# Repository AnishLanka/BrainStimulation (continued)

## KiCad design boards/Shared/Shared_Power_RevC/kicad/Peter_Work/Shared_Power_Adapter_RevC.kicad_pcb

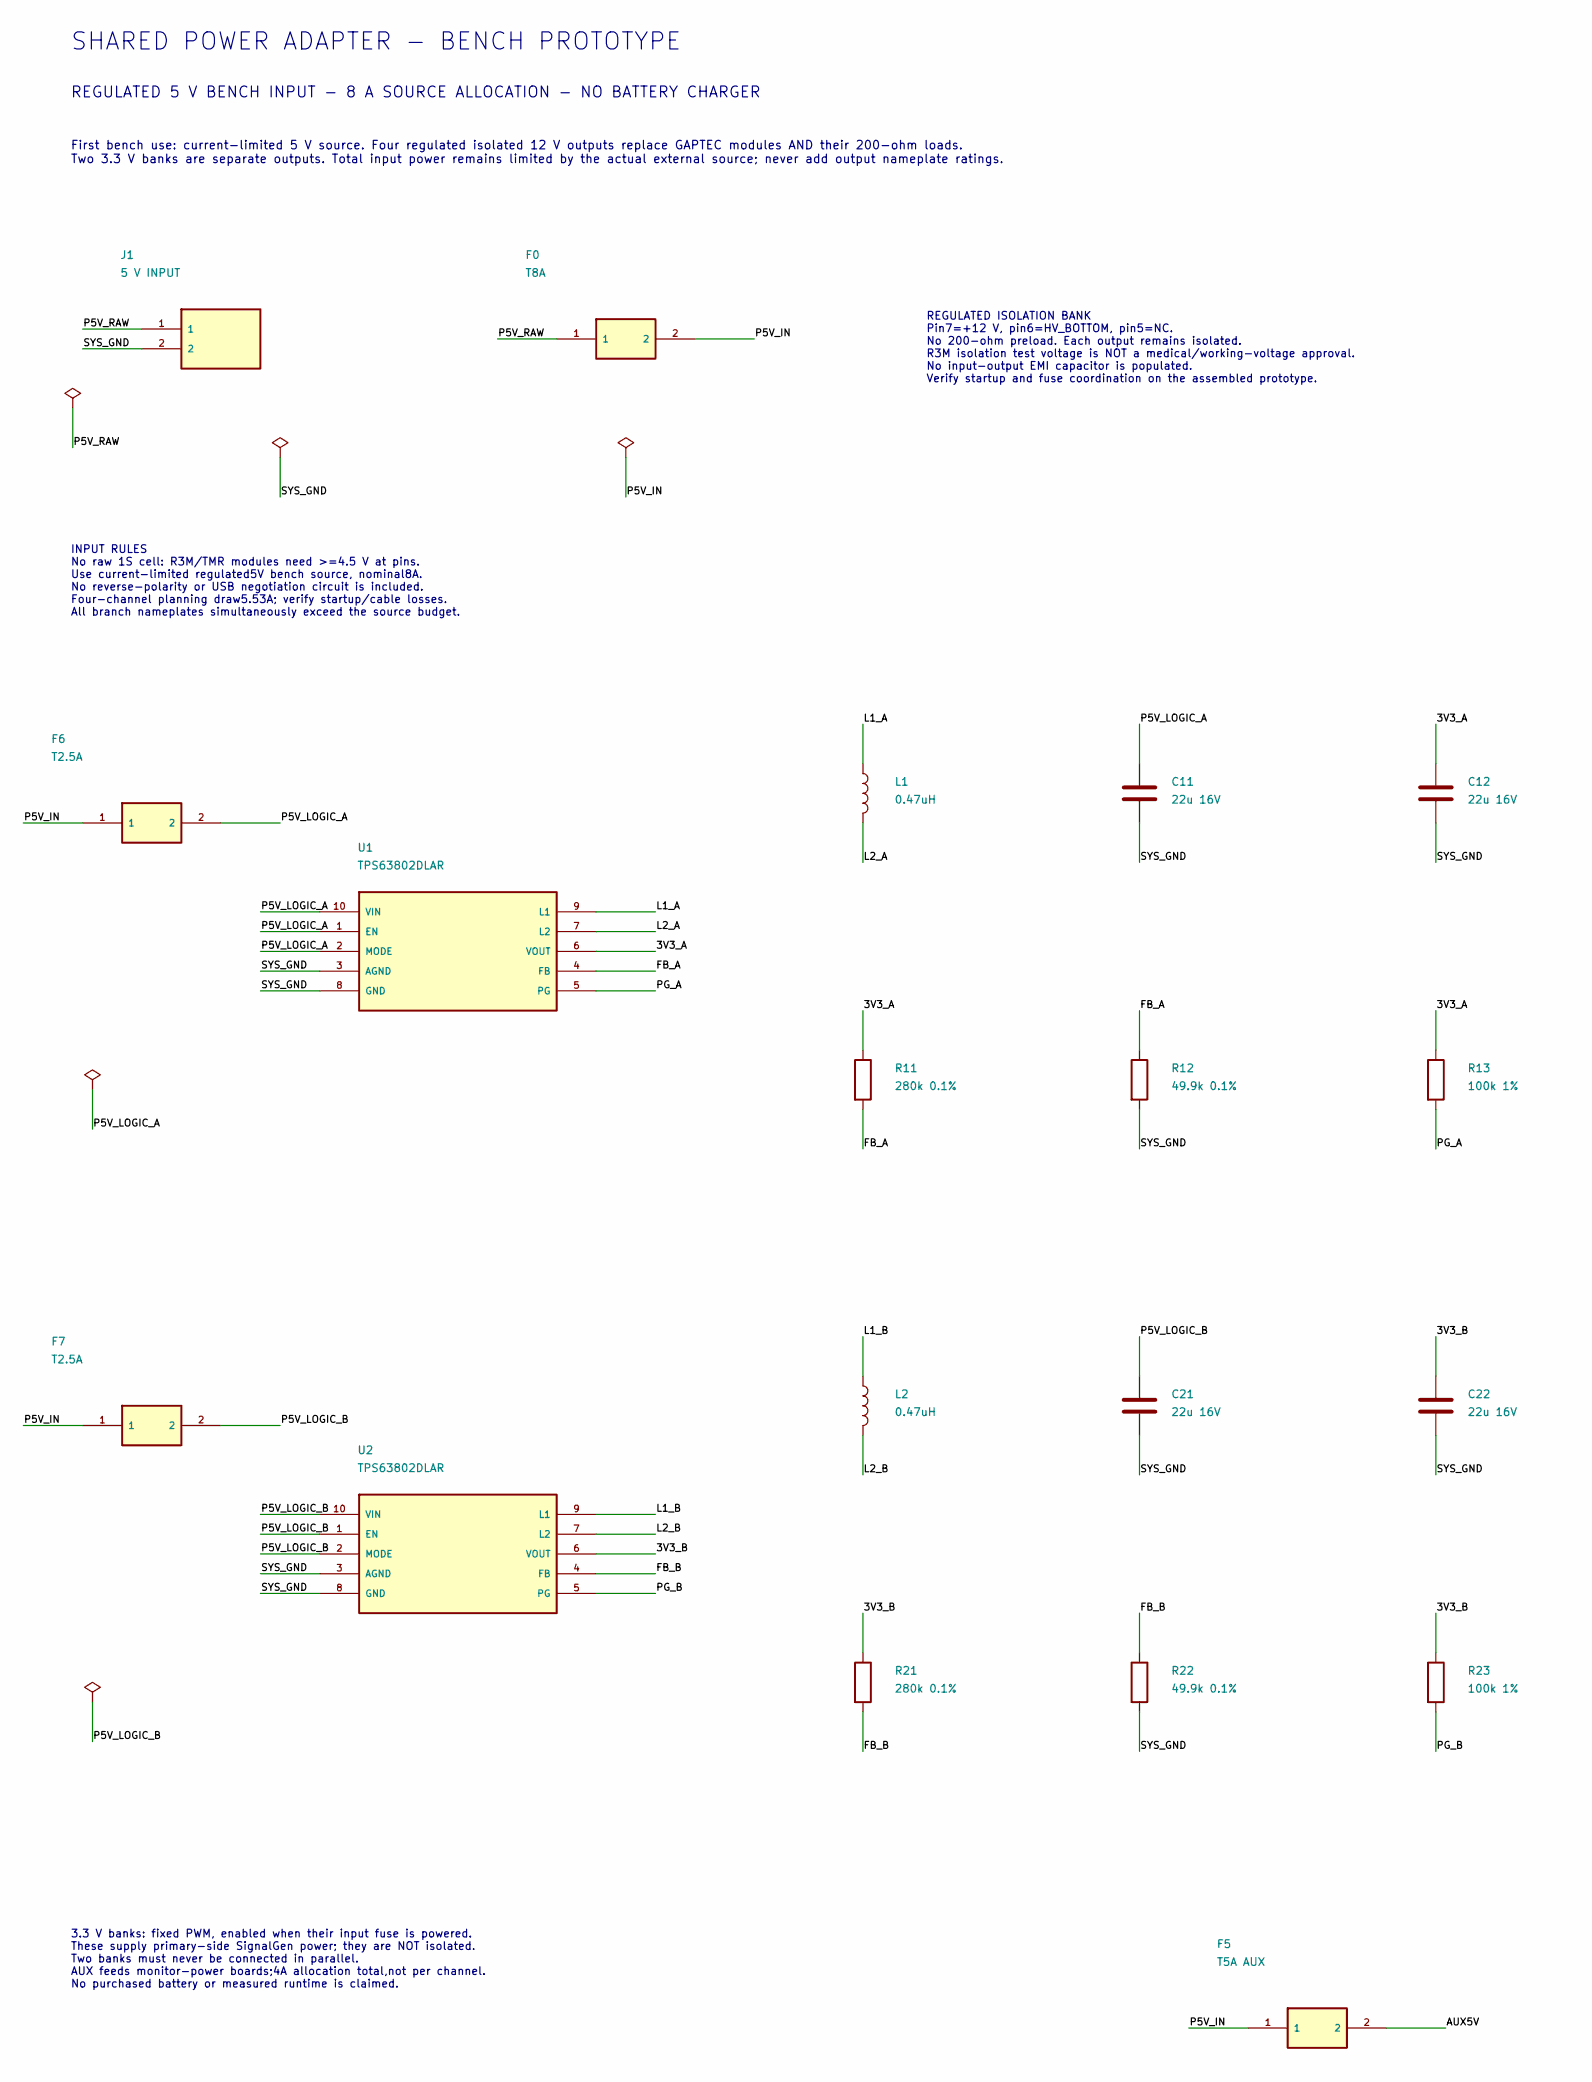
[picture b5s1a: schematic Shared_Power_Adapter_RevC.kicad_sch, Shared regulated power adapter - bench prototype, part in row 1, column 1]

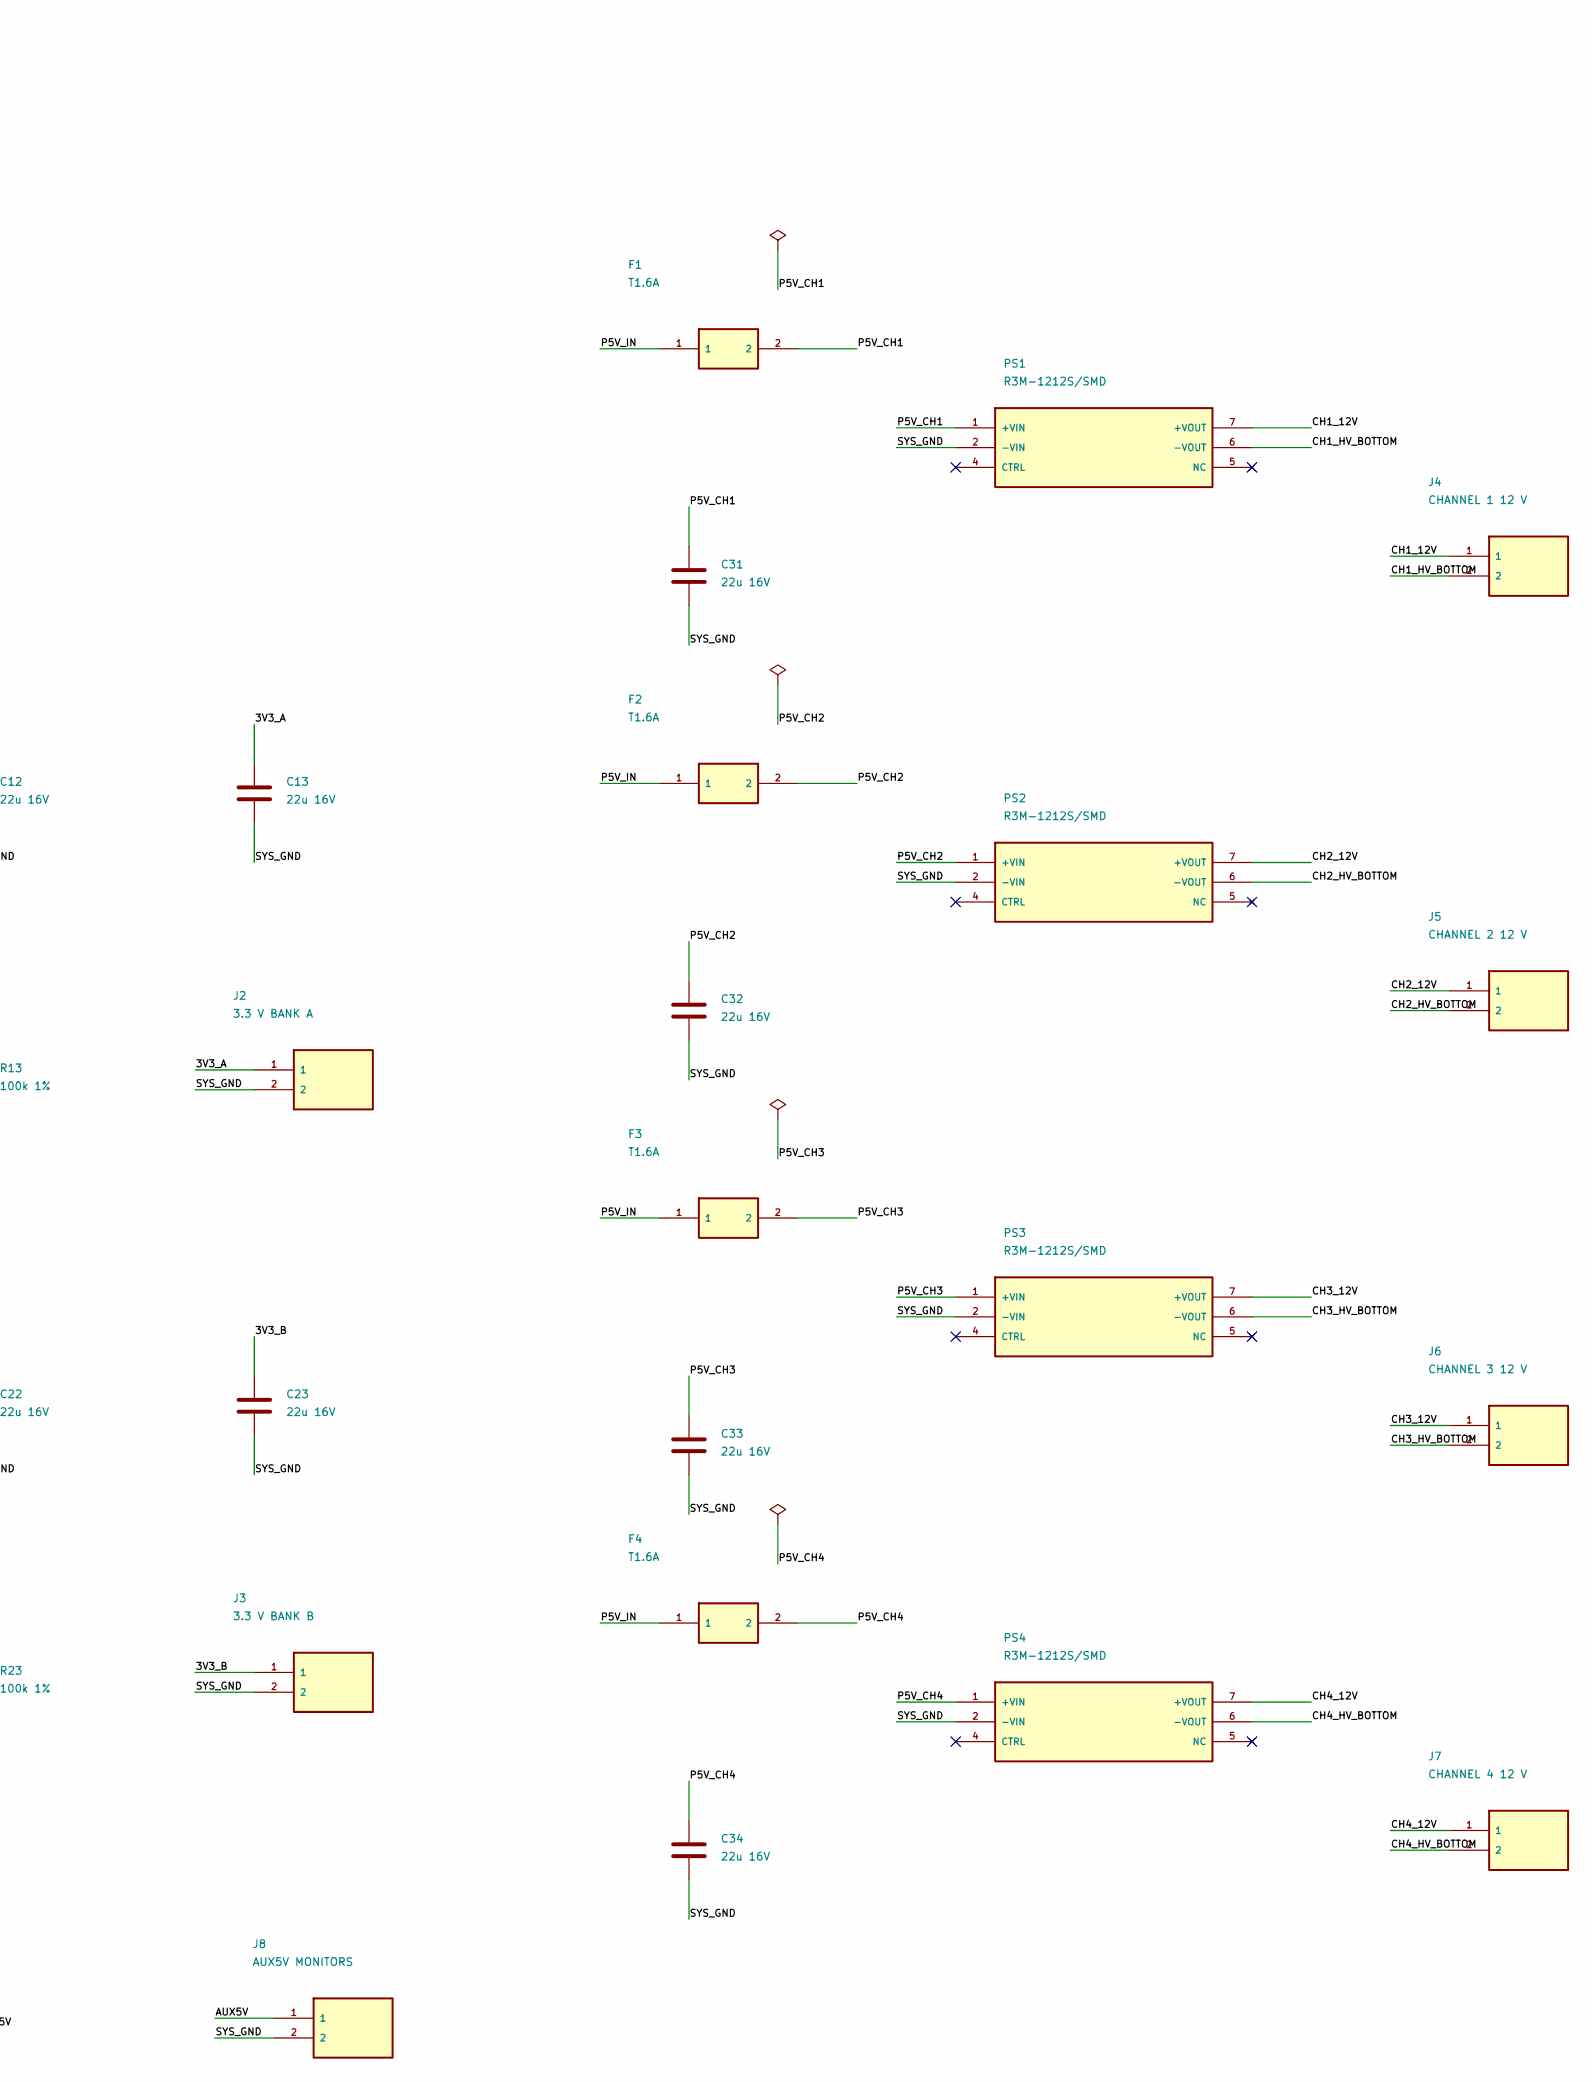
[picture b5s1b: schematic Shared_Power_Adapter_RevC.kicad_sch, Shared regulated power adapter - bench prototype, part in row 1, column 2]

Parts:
C11, C12, C13, C21, C22, C23, C31, C32, C33, C34: 22u 16V; C_1206_3216Metric; MPN GRM31CR61C226KE15L
F0: T8A; Fuse_Schurter_UMT250; MPN 3403.0175.11
F1, F2, F3, F4: T1.6A; Fuse_Schurter_UMT250; MPN 3403.0168.11
F5: T5A AUX; Fuse_Schurter_UMT250; MPN 3403.0173.11
F6, F7: T2.5A; Fuse_Schurter_UMT250; MPN 3403.0170.11
J1: 5 V INPUT; JST_VH_B2P-VH_1x02_P3.96mm_Vertical; MPN B2P-VH
J2: 3.3 V BANK A; JST_VH_B2P-VH_1x02_P3.96mm_Vertical; MPN B2P-VH
J3: 3.3 V BANK B; JST_VH_B2P-VH_1x02_P3.96mm_Vertical; MPN B2P-VH
J4: CHANNEL 1 12 V; JST_VH_B2P-VH_1x02_P3.96mm_Vertical; MPN B2P-VH
J5: CHANNEL 2 12 V; JST_VH_B2P-VH_1x02_P3.96mm_Vertical; MPN B2P-VH
J6: CHANNEL 3 12 V; JST_VH_B2P-VH_1x02_P3.96mm_Vertical; MPN B2P-VH
J7: CHANNEL 4 12 V; JST_VH_B2P-VH_1x02_P3.96mm_Vertical; MPN B2P-VH
J8: AUX5V MONITORS; JST_VH_B2P-VH_1x02_P3.96mm_Vertical; MPN B2P-VH
L1, L2: 0.47uH; L_Coilcraft_XFL4015; MPN XFL4015-471MEC
PS1, PS2, PS3, PS4: R3M-1212S/SMD; RECOM_R3M_SMD; MPN R3M-1212S/SMD
R11, R21: 280k 0.1%; R_0603_1608Metric; MPN TNPW0603280KBEEA
R12, R22: 49.9k 0.1%; R_0603_1608Metric; MPN TNPW060349K9BEEA
R13, R23: 100k 1%; R_0603_1608Metric; MPN CRCW0603100KFKEA
U1, U2: TPS63802DLAR; Texas_DLA0010A_TPS63802; MPN TPS63802DLAR

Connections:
/3V3_A: C12.1, C13.1, J2.1, R11.1, R13.1, U1.6 (VOUT)
/3V3_B: C22.1, C23.1, J3.1, R21.1, R23.1, U2.6 (VOUT)
/AUX5V: F5.2, J8.1
/CH1_12V: J4.1, PS1.7 (+VOUT)
/CH1_HV_BOTTOM: J4.2, PS1.6 (-VOUT)
/CH2_12V: J5.1, PS2.7 (+VOUT)
/CH2_HV_BOTTOM: J5.2, PS2.6 (-VOUT)
/CH3_12V: J6.1, PS3.7 (+VOUT)
/CH3_HV_BOTTOM: J6.2, PS3.6 (-VOUT)
/CH4_12V: J7.1, PS4.7 (+VOUT)
/CH4_HV_BOTTOM: J7.2, PS4.6 (-VOUT)
/FB_A: R11.2, R12.1, U1.4 (FB)
/FB_B: R21.2, R22.1, U2.4 (FB)
/L1_A: L1.1, U1.9 (L1)
/L1_B: L2.1, U2.9 (L1)
/L2_A: L1.2, U1.7 (L2)
/L2_B: L2.2, U2.7 (L2)
/P5V_CH1: C31.1, F1.2, PS1.1 (+VIN)
/P5V_CH2: C32.1, F2.2, PS2.1 (+VIN)
/P5V_CH3: C33.1, F3.2, PS3.1 (+VIN)
/P5V_CH4: C34.1, F4.2, PS4.1 (+VIN)
/P5V_IN: F0.2, F1.1, F2.1, F3.1, F4.1, F5.1, F6.1, F7.1
/P5V_LOGIC_A: C11.1, F6.2, U1.1 (EN), U1.2 (MODE), U1.10 (VIN)
/P5V_LOGIC_B: C21.1, F7.2, U2.1 (EN), U2.2 (MODE), U2.10 (VIN)
/P5V_RAW: F0.1, J1.1
/PG_A: R13.2, U1.5 (PG)
/PG_B: R23.2, U2.5 (PG)
/SYS_GND: C11.2, C12.2, C13.2, C21.2, C22.2, C23.2, C31.2, C32.2, C33.2, C34.2, J1.2, J2.2, J3.2, J8.2, PS1.2 (-VIN), PS2.2 (-VIN), PS3.2 (-VIN), PS4.2 (-VIN), R12.2, R22.2, U1.3 (AGND), U1.8 (GND), U2.3 (AGND), U2.8 (GND)

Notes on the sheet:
SHARED POWER ADAPTER - BENCH PROTOTYPE
REGULATED 5 V BENCH INPUT - 8 A SOURCE ALLOCATION - NO BATTERY CHARGER
First bench use: current-limited 5 V source. Four regulated isolated 12 V outputs replace GAPTEC modules AND their 200-ohm loads. Two 3.3 V banks are separate outputs. Total input power remains limited by the actual external source; never add output nameplate ratings.
INPUT RULES No raw 1S cell: R3M/TMR modules need >=4.5 V at pins. Use current-limited regulated5V bench source, nominal8A. No reverse-polarity or USB negotiation circuit is included. Four-channel planning draw5.53A; verify startup/cable losses. All branch nameplates simultaneously exceed the source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
3.3 V banks: fixed PWM, enabled when their input fuse is powered. These supply primary-side SignalGen power; they are NOT isolated. Two banks must never be connected in parallel. AUX feeds monitor-power boards;4A allocation total,not per channel. No purchased battery or measured runtime is claimed.
REGULATED ISOLATION BANK Pin7=+12 V, pin6=HV_BOTTOM, pin5=NC. No 200-ohm preload. Each output remains isolated. R3M isolation test voltage is NOT a medical/working-voltage approval. No input-output EMI capacitor is populated. Verify startup and fuse coordination on the assembled prototype.

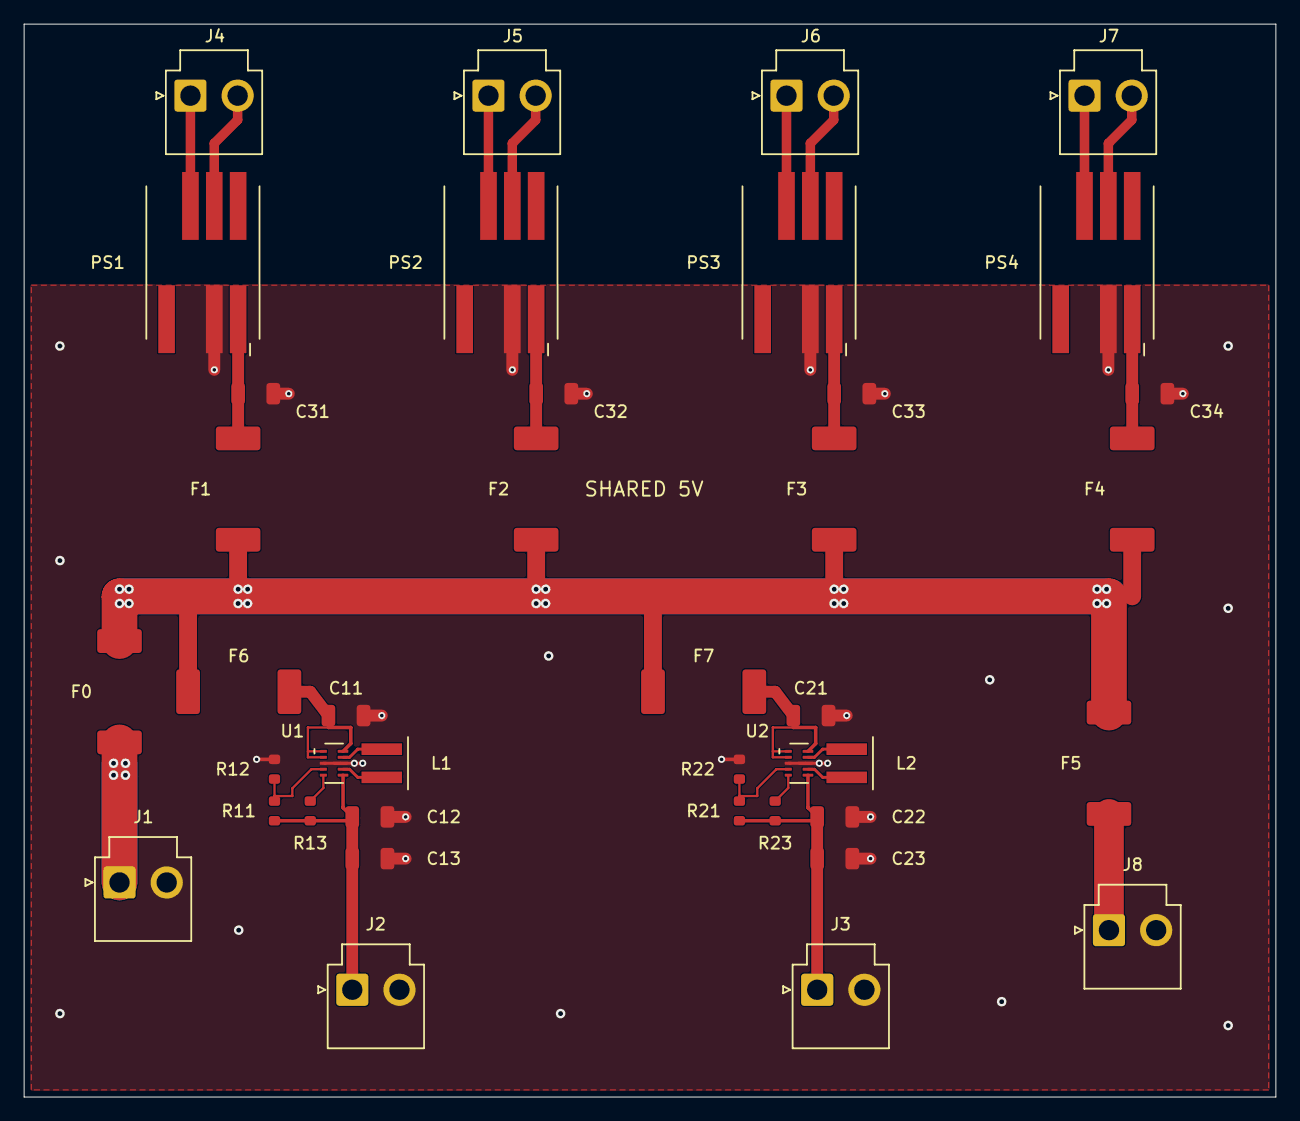
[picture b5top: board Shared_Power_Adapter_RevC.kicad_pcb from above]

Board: 2 copper layers, 105.0 x 90.0 mm, 40 parts (0 on the bottom side), 28 nets.

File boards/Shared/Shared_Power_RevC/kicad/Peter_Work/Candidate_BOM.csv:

Reference,Value,MPN,Footprint,Note,Source,DNP
J1,5 V INPUT,B2P-VH,PowerLocal:JST_VH_B2P-VH_1x02_P3.96mm_Vertical,"Regulated nominal5V, never above5.25V; module pins>=4.5V after fuse/cable drops. External8A current-limited source;16AWG harness,VHR-2N housing,SVH-41T-P1.1 contacts. Source capacity is not a measured PCB rating.",https://www.jst-mfg.com/product/index.php?lang=2&series=262,False
F0,T8A,3403.0175.11,PowerLocal:Fuse_Schurter_UMT250,Main input time-lag fuse; branch allocation applies; source current limit required.,https://www.schurter.com/en/datasheet/typ_UMT_250.pdf,False
F6,T2.5A,3403.0170.11,PowerLocal:Fuse_Schurter_UMT250,"Input branch fuse,2A maximum3.3V bank allocation; startup coordination must be measured.",https://www.schurter.com/en/datasheet/typ_UMT_250.pdf,False
U1,TPS63802DLAR,TPS63802DLAR,PowerLocal:Texas_DLA0010A_TPS63802,ExactTI DLA0010A land pattern; no invented exposed pad.,https://www.ti.com/lit/ds/symlink/tps63802.pdf,False
L1,0.47uH,XFL4015-471MEC,PowerLocal:L_Coilcraft_XFL4015,"Exact manufacturer lands .98x3.4mm,2.37mm center pitch.",https://www.ti.com/lit/ds/symlink/tps63802.pdf,False
C11,22u 16V,GRM31CR61C226KE15L,PowerLocal:C_1206_3216Metric,Input; verify >=5uF effective at5.25V and temperature.,https://www.ti.com/lit/pdf/tidrmp4,False
C12,22u 16V,GRM31CR61C226KE15L,PowerLocal:C_1206_3216Metric,Two parallel output caps; acceptance >=14uF effective total at 3.3V.,https://www.ti.com/lit/pdf/tidrmp4,False
C13,22u 16V,GRM31CR61C226KE15L,PowerLocal:C_1206_3216Metric,Two parallel output caps; acceptance >=14uF effective total at 3.3V.,https://www.ti.com/lit/pdf/tidrmp4,False
R11,280k 0.1%,TNPW0603280KBEEA,PowerLocal:R_0603_1608Metric,"Within manufacturer0603 range<=332k; .5*(1+280/49.9)=3.30561V nominal. 25ppm/K,standardEA packaging.",https://www.vishay.com/docs/28758/tnpw_e3.pdf,False
R12,49.9k 0.1%,TNPW060349K9BEEA,PowerLocal:R_0603_1608Metric,"Low-side divider<100k perTI;25ppm/K,standardEA packaging.",https://www.vishay.com/docs/28758/tnpw_e3.pdf,False
R13,100k 1%,CRCW0603100KFKEA,PowerLocal:R_0603_1608Metric,PG pullup; output indicator only.,https://www.ti.com/lit/ds/symlink/tps63802.pdf,False
J2,3.3 V BANK A,B2P-VH,PowerLocal:JST_VH_B2P-VH_1x02_P3.96mm_Vertical,"Dedicated dual-channel SignalGen supply; never parallel with other bank. Bank A design target2A, subject to source/thermal budget.",,False
F7,T2.5A,3403.0170.11,PowerLocal:Fuse_Schurter_UMT250,"Input branch fuse,2A maximum3.3V bank allocation; startup coordination must be measured.",https://www.schurter.com/en/datasheet/typ_UMT_250.pdf,False
U2,TPS63802DLAR,TPS63802DLAR,PowerLocal:Texas_DLA0010A_TPS63802,ExactTI DLA0010A land pattern; no invented exposed pad.,https://www.ti.com/lit/ds/symlink/tps63802.pdf,False
L2,0.47uH,XFL4015-471MEC,PowerLocal:L_Coilcraft_XFL4015,"Exact manufacturer lands .98x3.4mm,2.37mm center pitch.",https://www.ti.com/lit/ds/symlink/tps63802.pdf,False
C21,22u 16V,GRM31CR61C226KE15L,PowerLocal:C_1206_3216Metric,Input; verify >=5uF effective at5.25V and temperature.,https://www.ti.com/lit/pdf/tidrmp4,False
C22,22u 16V,GRM31CR61C226KE15L,PowerLocal:C_1206_3216Metric,Two parallel output caps; acceptance >=14uF effective total at 3.3V.,https://www.ti.com/lit/pdf/tidrmp4,False
C23,22u 16V,GRM31CR61C226KE15L,PowerLocal:C_1206_3216Metric,Two parallel output caps; acceptance >=14uF effective total at 3.3V.,https://www.ti.com/lit/pdf/tidrmp4,False
R21,280k 0.1%,TNPW0603280KBEEA,PowerLocal:R_0603_1608Metric,"Within manufacturer0603 range<=332k; .5*(1+280/49.9)=3.30561V nominal. 25ppm/K,standardEA packaging.",https://www.vishay.com/docs/28758/tnpw_e3.pdf,False
R22,49.9k 0.1%,TNPW060349K9BEEA,PowerLocal:R_0603_1608Metric,"Low-side divider<100k perTI;25ppm/K,standardEA packaging.",https://www.vishay.com/docs/28758/tnpw_e3.pdf,False
R23,100k 1%,CRCW0603100KFKEA,PowerLocal:R_0603_1608Metric,PG pullup; output indicator only.,https://www.ti.com/lit/ds/symlink/tps63802.pdf,False
J3,3.3 V BANK B,B2P-VH,PowerLocal:JST_VH_B2P-VH_1x02_P3.96mm_Vertical,"Dedicated dual-channel SignalGen supply; never parallel with other bank. Bank B design target2A, subject to source/thermal budget.",,False
F1,T1.6A,3403.0168.11,PowerLocal:Fuse_Schurter_UMT250,RECOM recommendedT1.6A for12Vin family; exact5V startup/fault coordination remains measured acceptance.,https://www.schurter.com/en/datasheet/typ_UMT_250.pdf,False
PS1,R3M-1212S/SMD,R3M-1212S/SMD,PowerLocal:RECOM_R3M_SMD,"ExactECO5 manufacturer lands; no minimum load; CTRL open enables. Pin5 NC,pin6 return.",https://recom-power.com/pdf/Econoline/R3M.pdf,False
J4,CHANNEL 1 12 V,B2P-VH,PowerLocal:JST_VH_B2P-VH_1x02_P3.96mm_Vertical,"Connect to boost IN only. Return is HV_BOTTOM, never MID; no connection across channels.",,False
C31,22u 16V,GRM31CR61C226KE15L,PowerLocal:C_1206_3216Metric,Local input bypass; EMI filter is not yet designed.,https://www.ti.com/lit/pdf/tidrmp4,False
F2,T1.6A,3403.0168.11,PowerLocal:Fuse_Schurter_UMT250,RECOM recommendedT1.6A for12Vin family; exact5V startup/fault coordination remains measured acceptance.,https://www.schurter.com/en/datasheet/typ_UMT_250.pdf,False
PS2,R3M-1212S/SMD,R3M-1212S/SMD,PowerLocal:RECOM_R3M_SMD,"ExactECO5 manufacturer lands; no minimum load; CTRL open enables. Pin5 NC,pin6 return.",https://recom-power.com/pdf/Econoline/R3M.pdf,False
J5,CHANNEL 2 12 V,B2P-VH,PowerLocal:JST_VH_B2P-VH_1x02_P3.96mm_Vertical,"Connect to boost IN only. Return is HV_BOTTOM, never MID; no connection across channels.",,False
C32,22u 16V,GRM31CR61C226KE15L,PowerLocal:C_1206_3216Metric,Local input bypass; EMI filter is not yet designed.,https://www.ti.com/lit/pdf/tidrmp4,False
F3,T1.6A,3403.0168.11,PowerLocal:Fuse_Schurter_UMT250,RECOM recommendedT1.6A for12Vin family; exact5V startup/fault coordination remains measured acceptance.,https://www.schurter.com/en/datasheet/typ_UMT_250.pdf,False
PS3,R3M-1212S/SMD,R3M-1212S/SMD,PowerLocal:RECOM_R3M_SMD,"ExactECO5 manufacturer lands; no minimum load; CTRL open enables. Pin5 NC,pin6 return.",https://recom-power.com/pdf/Econoline/R3M.pdf,False
J6,CHANNEL 3 12 V,B2P-VH,PowerLocal:JST_VH_B2P-VH_1x02_P3.96mm_Vertical,"Connect to boost IN only. Return is HV_BOTTOM, never MID; no connection across channels.",,False
C33,22u 16V,GRM31CR61C226KE15L,PowerLocal:C_1206_3216Metric,Local input bypass; EMI filter is not yet designed.,https://www.ti.com/lit/pdf/tidrmp4,False
F4,T1.6A,3403.0168.11,PowerLocal:Fuse_Schurter_UMT250,RECOM recommendedT1.6A for12Vin family; exact5V startup/fault coordination remains measured acceptance.,https://www.schurter.com/en/datasheet/typ_UMT_250.pdf,False
PS4,R3M-1212S/SMD,R3M-1212S/SMD,PowerLocal:RECOM_R3M_SMD,"ExactECO5 manufacturer lands; no minimum load; CTRL open enables. Pin5 NC,pin6 return.",https://recom-power.com/pdf/Econoline/R3M.pdf,False
J7,CHANNEL 4 12 V,B2P-VH,PowerLocal:JST_VH_B2P-VH_1x02_P3.96mm_Vertical,"Connect to boost IN only. Return is HV_BOTTOM, never MID; no connection across channels.",,False
C34,22u 16V,GRM31CR61C226KE15L,PowerLocal:C_1206_3216Metric,Local input bypass; EMI filter is not yet designed.,https://www.ti.com/lit/pdf/tidrmp4,False
F5,T5A AUX,3403.0173.11,PowerLocal:Fuse_Schurter_UMT250,"Four-channel monitor bank4A allocation,3.073A planning. Fuse is not an electronic current limit.",https://www.schurter.com/en/datasheet/typ_UMT_250.pdf,False
J8,AUX5V MONITORS,B2P-VH,PowerLocal:JST_VH_B2P-VH_1x02_P3.96mm_Vertical,4A total AUX allocation; powers all monitor powerboards from common primarySYS_GND. Verifymoduleinputs>=4.5V afterallfuses/cables.,,False

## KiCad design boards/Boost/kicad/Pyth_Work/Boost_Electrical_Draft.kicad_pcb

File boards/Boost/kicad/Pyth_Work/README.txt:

79.7 V BOOST - ENGINEERING BENCH PROTOTYPE

Open Boost_Electrical_Draft.kicad_pro in KiCad10. The schematic, PCB and local libraries
are included. The routed PCB matches the schematic and passes the checks in
PCB_DRC.json / PCB_Validation.json. Read PCB_Draft_Notes.txt for mechanics,
pinout and layout decisions, Draft_Review.txt for electrical assumptions, and
Fabrication_Order_Notes.txt for the0.4 mm bare-board order. The top-level upload
archive is Boost_79V7_Prototype_JLCPCB.zip. The hardware still requires assembly and bench testing.

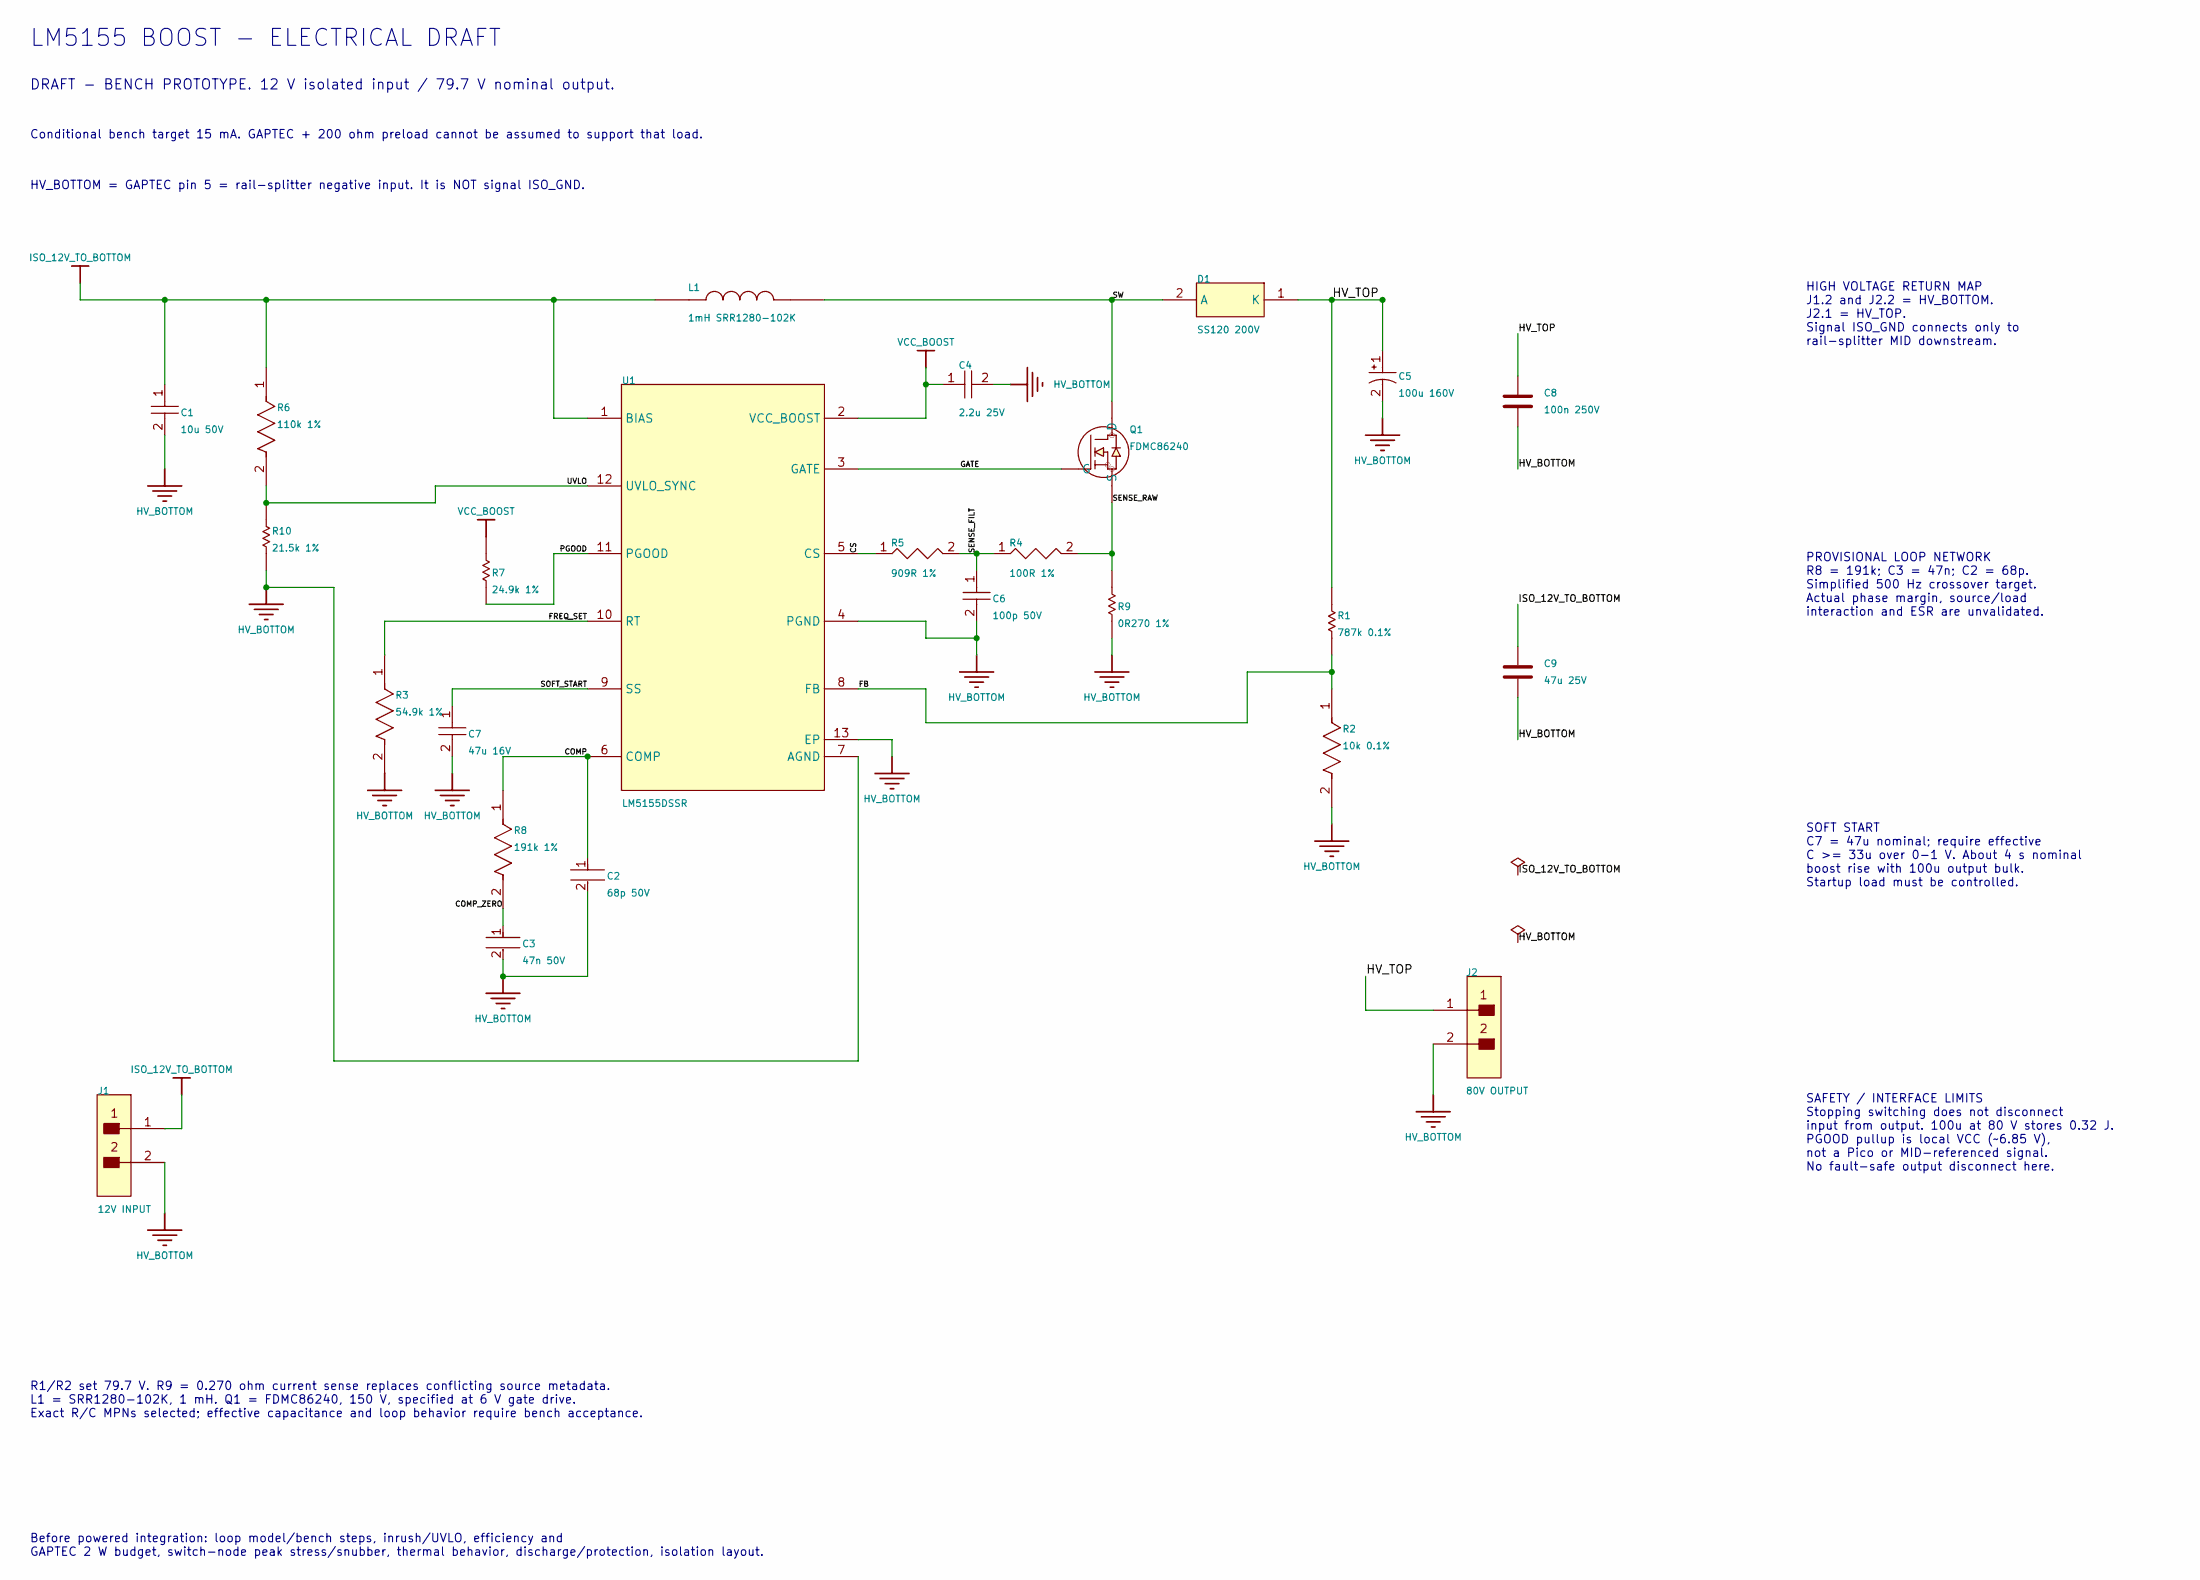
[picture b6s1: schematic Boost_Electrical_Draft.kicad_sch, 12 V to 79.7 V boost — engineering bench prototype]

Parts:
C1: 10u 50V; C0805; Rating 0805;10uF10%;50V;-55 to85C; MPN C2012X5R1H106K125AC
C2: 68p 50V; C0603; Rating 0603;68pF5%;50V; MPN C1608C0G1H680J080AA
C3: 47n 50V; C0603; Rating 0603;47nF10%;50V; MPN C1608X7R1H473K080AA
C4: 2.2u 25V; C0805; Rating 0805;2.2uF10%;25V; MPN C2012X7R1E225K125AB
C5: 100u 160V; C_BULK; Rating 100uF20%;160V;105C;D16mm;H20mm;P7.5mm;l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; MPN EEUEE2C101S
C6: 100p 50V; C0603; Rating 0603;100pF5%;50V; MPN C1608C0G1H101J080AA
C7: 47u 16V; C1210; Rating 1210;47uF10%;16V;-55 to85C; MPN GRM32ER61C476KE15L
C8: 100n 250V; C0805; Rating 0805;100nF10%;250V; MPN C2012X7T2E104K125AA
C9: 47u 25V; C1210; Rating 1210;47uF20%;25V;-55 to85C; MPN MSAST32MAB5476MPNDT1
D1: SS120 200V; D_SMA; Rating 200V,1A Schottky; verify order suffix; MPN SS120
J1: 12V INPUT; IN_FP-TSW-102-14-G-S-MFG
J2: 80V OUTPUT; OUT_FP-TSW-102-14-G-S-MFG
L1: 1mH SRR1280-102K; L_BOURNS; Rating 1mH10%;DCR1.7ohm max;Irms0.68A;Isat0.80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; MPN SRR1280-102K
Q1: FDMC86240; Q_FDMC86240_CASE511DH; Rating 150V;RDS(on) 70mohm max at VGS 6V; WDFN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; MPN FDMC86240
R1: 787k 0.1%; R1206; Rating 1206; 200V working; at least 0.25W; 0.1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; MPN TNPW1206787KBEEA
R2: 10k 0.1%; R0603; Rating 0603;100V working;at least0.1W;0.1%;25p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; MPN TNPW060310K0BEEA
R3: 54.9k 1%; R0603; Rating 0603;1%;100ppm/K;0.1W;75V; MPN CRCW060354K9FKEA
R4: 100R 1%; R0603; Rating 0603;1%;100ppm/K;0.1W;75V; MPN CRCW0603100RFKEA
R5: 909R 1%; R0603; Rating 0603;1%;100ppm/K;0.1W;75V; MPN CRCW0603909RFKEA
R6: 110k 1%; R0603; Rating 0603;1%;100ppm/K;0.1W;75V; MPN CRCW0603110KFKEA
R7: 24.9k 1%; R0603; Rating 0603;1%;100ppm/K;0.1W;75V; MPN CRCW060324K9FKEA
R8: 191k 1%; R0805; Rating 0805;1%;100ppm/K;0.125W;150V; MPN CRCW0805191KFKEA
R9: 0R270 1%; R1206; Rating 1206;0.270ohm1%;0.5W at70C;derate above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; MPN ERJ8BQFR27V
R10: 21.5k 1%; R0603; Rating 0603;1%;100ppm/K;0.1W;75V; MPN CRCW060321K5FKEA
U1: LM5155DSSR; U1_DSS0012B; MPN LM5155DSSR

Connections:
/COMP: C2.1, R8.1, U1.6 (COMP)
/COMP_ZERO: C3.1, R8.2
/CS: R5.1, U1.5 (CS)
/FB: R1.2, R2.1, U1.8 (FB)
/FREQ_SET: R3.1, U1.10 (RT)
/GATE: Q1.4 (G), U1.3 (GATE)
/HV_TOP: C5.1, C8.1, D1.1 (K), J2.1, R1.1
/PGOOD: R7.1, U1.11 (PGOOD)
/SENSE_FILT: C6.1, R4.1, R5.2
/SENSE_RAW: Q1.1 (S), Q1.2 (S), Q1.3 (S), R4.2, R9.2
/SOFT_START: C7.1, U1.9 (SS)
/SW: D1.2 (A), L1.2, Q1.5 (D), Q1.6 (D), Q1.7 (D), Q1.8 (D)
/UVLO: R6.2, R10.1, U1.12 (UVLO_SYNC)
HV_BOTTOM: C1.2, C2.2, C3.2, C4.2, C5.2, C6.2, C7.2, C8.2, C9.2, J1.2, J2.2, R2.2, R3.2, R9.1, R10.2, U1.4 (PGND), U1.7 (AGND), U1.13 (EP)
ISO_12V_TO_BOTTOM: C1.1, C9.1, J1.1, L1.1, R6.1, U1.1 (BIAS)
VCC_BOOST: C4.1, R7.2, U1.2 (VCC_BOOST)

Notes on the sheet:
LM5155 BOOST - ELECTRICAL DRAFT
DRAFT - BENCH PROTOTYPE. 12 V isolated input / 79.7 V nominal output.
Conditional bench target 15 mA. GAPTEC + 200 ohm preload cannot be assumed to support that load.
HV_BOTTOM = GAPTEC pin 5 = rail-splitter negative input. It is NOT signal ISO_GND.
HIGH VOLTAGE RETURN MAP J1.2 and J2.2 = HV_BOTTOM. J2.1 = HV_TOP. Signal ISO_GND connects only to rail-splitter MID downstream.
PROVISIONAL LOOP NETWORK R8 = 191k; C3 = 47n; C2 = 68p. Simplified 500 Hz crossover target. Actual phase margin, source/load interaction and ESR are unvalidated.
SOFT START C7 = 47u nominal; require effective C >= 33u over 0-1 V. About 4 s nominal boost rise with 100u output bulk. Startup load must be controlled.
SAFETY / INTERFACE LIMITS Stopping switching does not disconnect input from output. 100u at 80 V stores 0.32 J. PGOOD pullup is local VCC (~6.85 V), not a Pico or MID-referenced signal. No fault-safe output disconnect here.
R1/R2 set 79.7 V. R9 = 0.270 ohm current sense replaces conflicting source metadata. L1 = SRR1280-102K, 1 mH. Q1 = FDMC86240, 150 V, specified at 6 V gate drive. Exact R/C MPNs selected; effective capacitance and loop behavior require bench acceptance.
Before powered integration: loop model/bench steps, inrush/UVLO, efficiency and GAPTEC 2 W budget, switch-node peak stress/snubber, thermal behavior, discharge/protection, isolation layout.

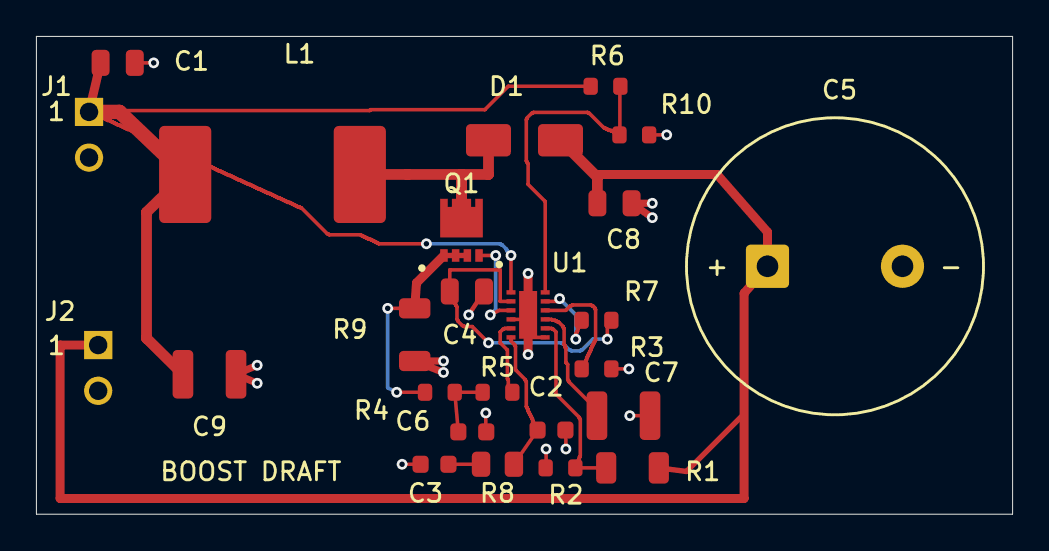
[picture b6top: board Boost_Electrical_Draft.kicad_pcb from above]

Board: 2 copper layers, 54.2 x 26.5 mm, 25 parts (0 on the bottom side), 16 nets.
